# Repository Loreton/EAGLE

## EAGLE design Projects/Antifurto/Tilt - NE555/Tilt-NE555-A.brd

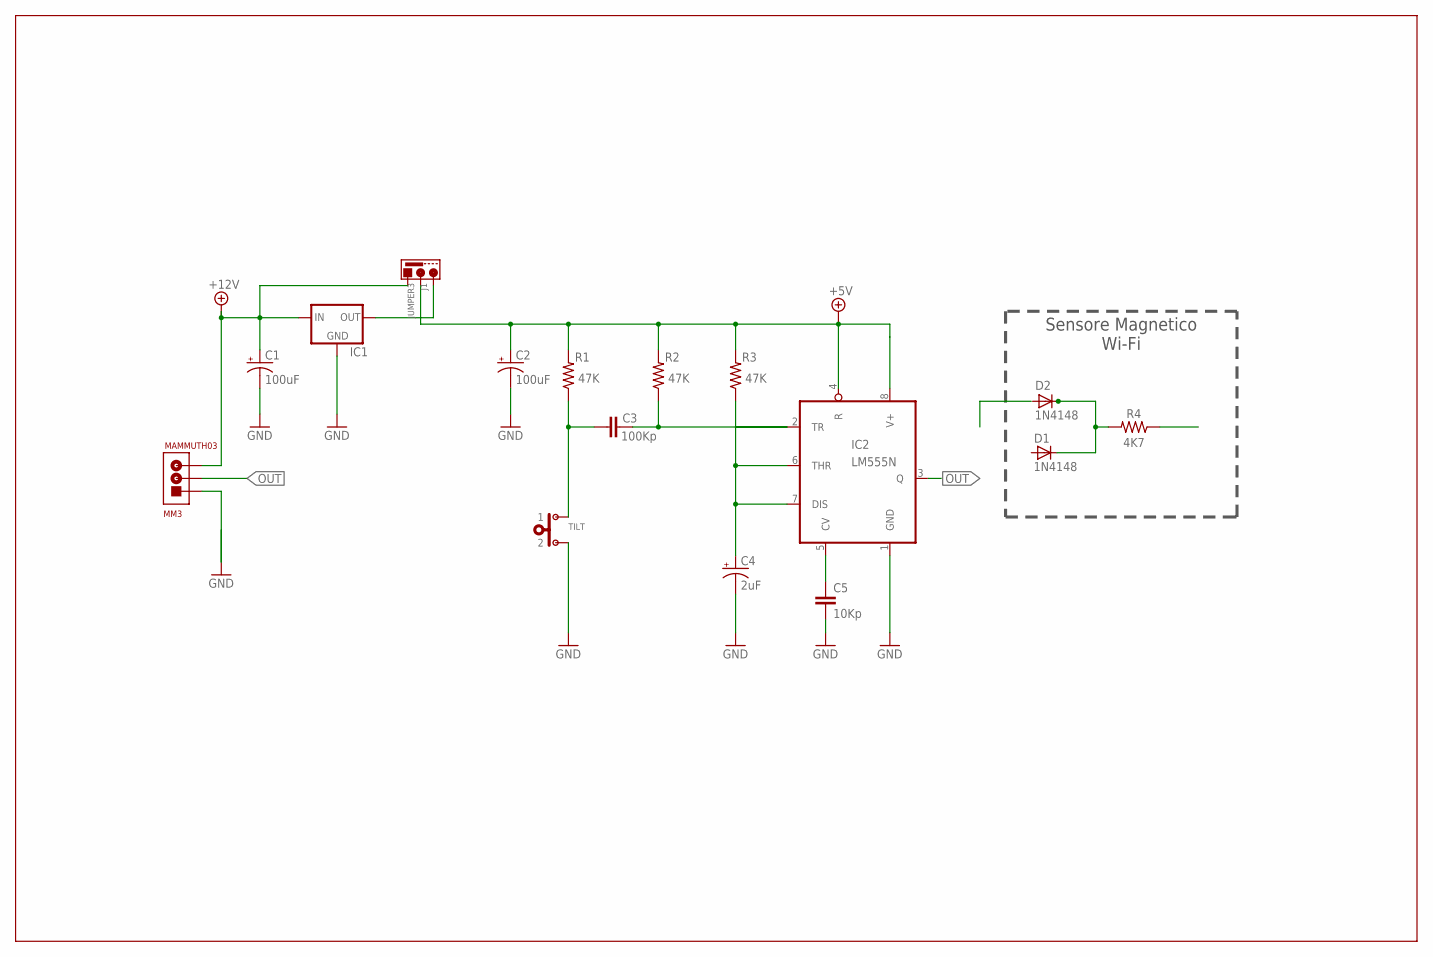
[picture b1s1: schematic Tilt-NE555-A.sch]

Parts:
C1, C2: 100uF; 085CS_1AR
C3: 100Kp; C025-025X050
C4: 2uF; 085CS_1AR
C5: 10Kp; C025-025X050
D1, D2: 1N4148; DO35-10
IC1: 78LXX
IC2: LM555N; DIL08
J1: JUMPER3; SIP03
MM3: MAMMUTH03
R1, R2, R3: 47K; 0207/12
R4: 4K7; 0207/12
TILT: PULSANTENO; SIP02

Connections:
+5V: C2.+, IC2.4 (R), IC2.8 (V+), J1.1, R1.2, R2.2, R3.2
+12V: C1.+, IC1.IN, J1.2, MM3.P$3 (3)
GND: C1.-, C2.-, C4.-, C5.2, IC1.GND, IC2.1 (GND), MM3.P$1 (1), TILT.2
unnamed: C3.2, IC2.2 (TR), R2.1
unnamed: C3.1, R1.1, TILT.1
unnamed: C4.+, IC2.6 (THR), IC2.7 (DIS), R3.1
unnamed: C5.1, IC2.5 (CV)
unnamed: D1.C, D2.C, R4.2
unnamed: IC1.OUT, J1.3
OUT: IC2.3 (Q), MM3.P$2 (2)
SENSORE: R4.1

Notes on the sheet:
Sensore Magnetico Wi-Fi

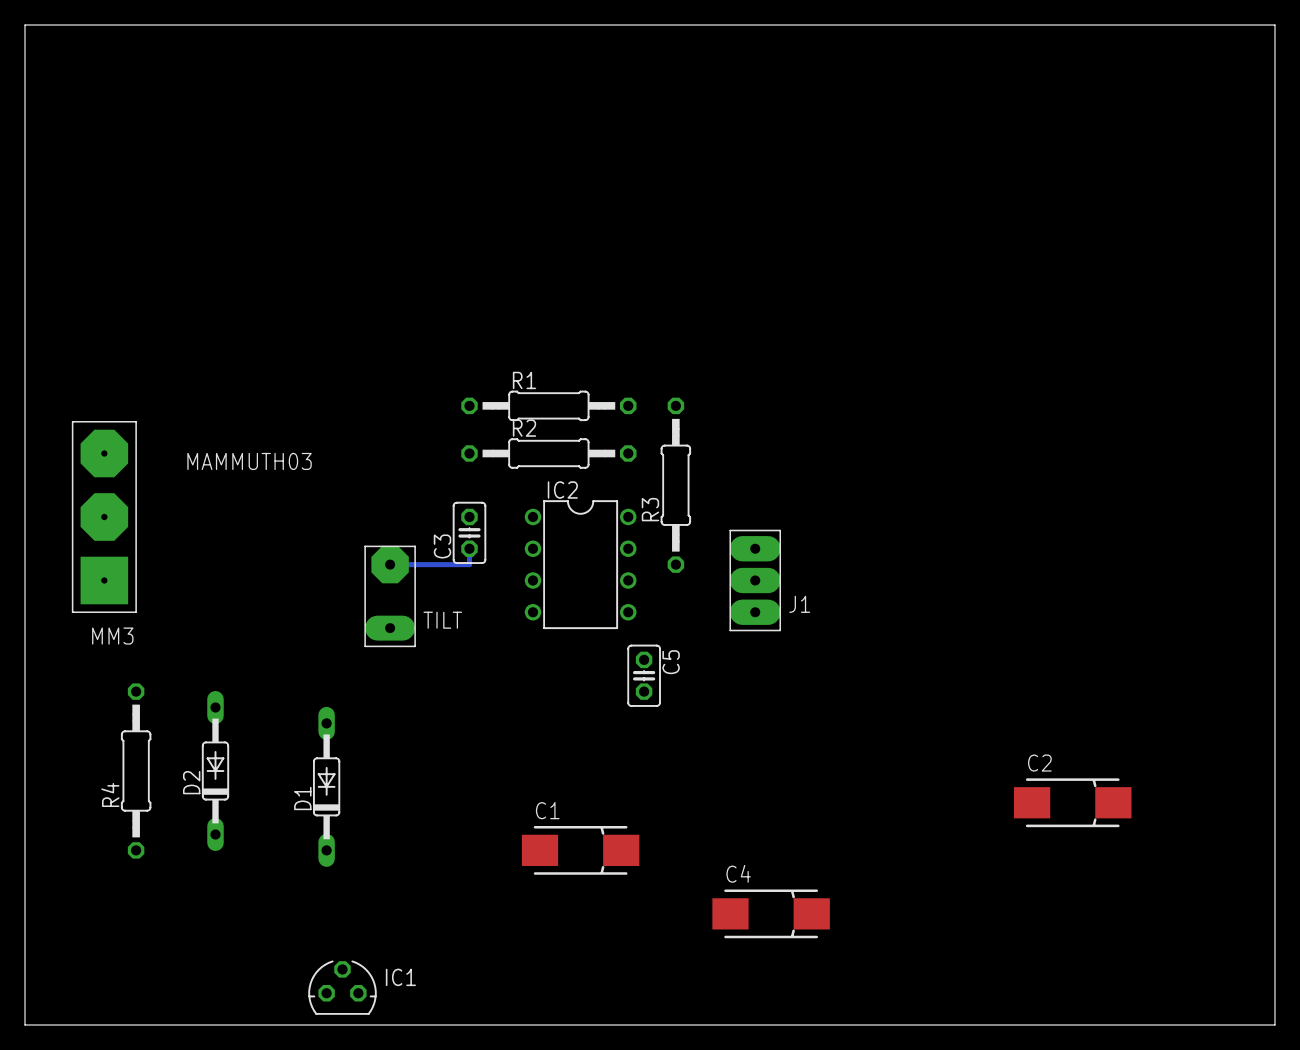
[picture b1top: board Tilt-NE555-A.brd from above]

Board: 2 copper layers, 100.0 x 80.0 mm, 16 parts (0 on the bottom side), 10 nets.

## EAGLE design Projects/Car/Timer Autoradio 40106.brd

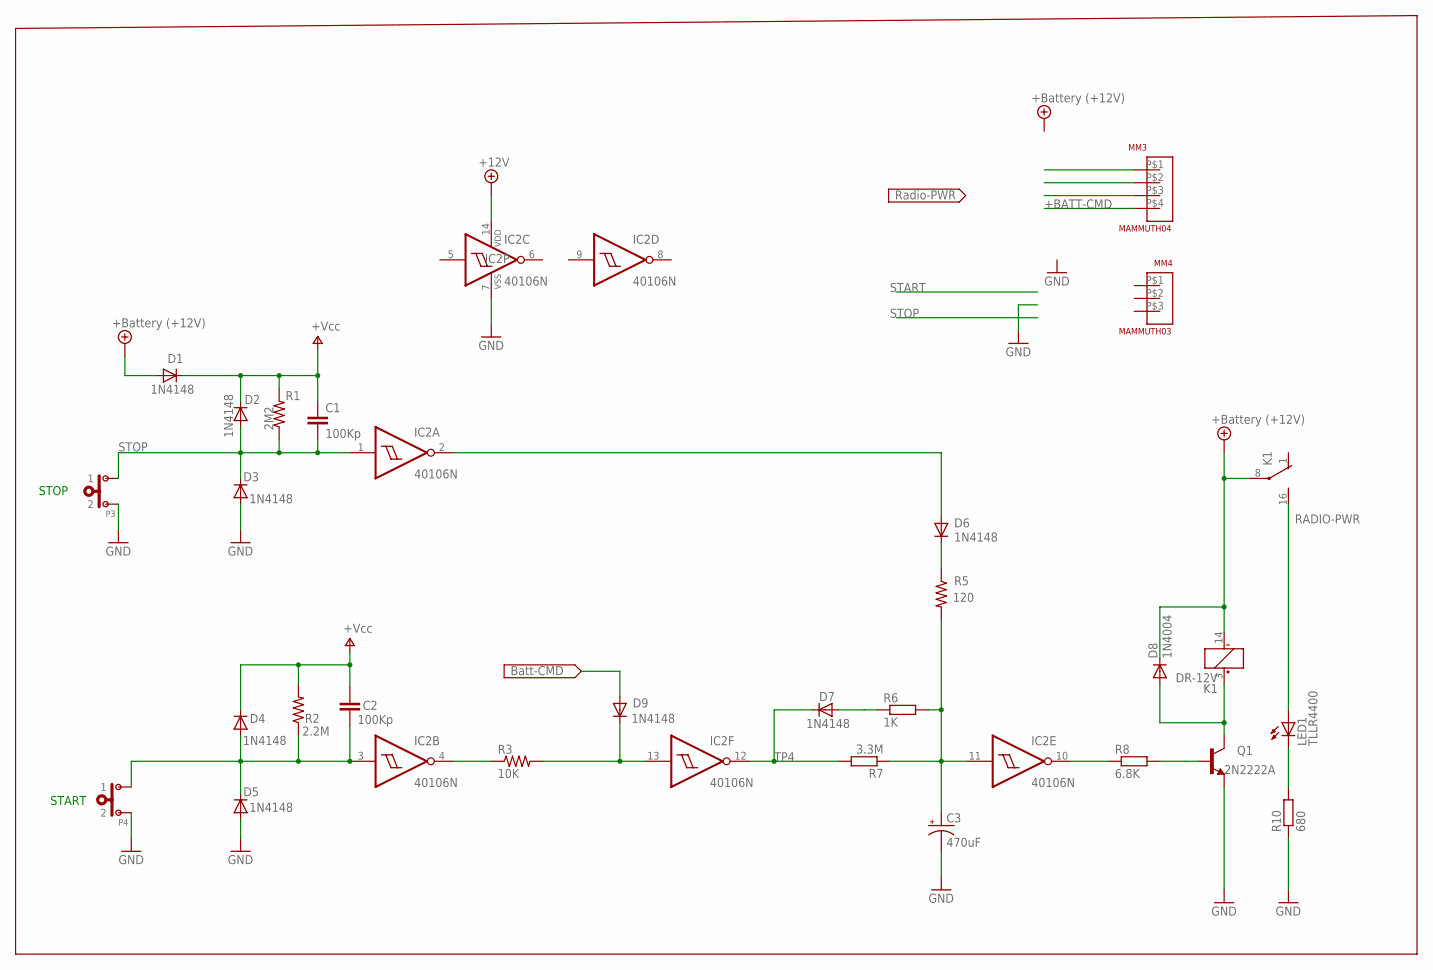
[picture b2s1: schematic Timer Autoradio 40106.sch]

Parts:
C1, C2: 100Kp; C025-025X050
C3: 470uF; E3,5-8
D1, D2, D3, D4, D5, D6, D7, D9: 1N4148; DO35-10
D8: 1N4004; DO41-10
IC2: 40106N; DIL14
K1: DR-12V; DR-1
LED1: TLLR4400; LED3MM
MM3: MAMMUTH04
MM4: MAMMUTH03
P3, P4: PULSANTENO; SIP02
Q1: 2N2222A; TO18
R1: 2M2; 0207/12
R2: 2.2M; 0207/12
R3: 10K; 0207/12
R5: 120; 0207/12
R6: 1K; 0207/10
R7: 3.3M; 0207/10
R8: 6.8K; 0207/10
R10: 680; 0207/10

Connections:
+12V: D1.A, D8.C, IC2.14 (VDD), K1.8, K1.14 (-)
+BATT-CMD: D9.C, R3.2
GND: C3.-, D3.A, D5.A, IC2.7 (VSS), P3.2, P4.2, Q1.1 (E), R10.1
unnamed: C2.2, D4.A, D5.C, IC2.3 (I), P4.1, R2.1
unnamed: Q1.2 (B), R8.2
unnamed: D8.A, K1.3 (+), Q1.3 (C)
unnamed: D6.C, R5.1
unnamed: LED1.K (C), R10.2
RADIO-PWR: K1.16 (S), LED1.A
START: D7.A, R6.1
STOP: C1.2, D2.A, D3.C, IC2.1 (I), P3.1, R1.1
TP4: D7.C, R7.2
TP4A: C3.+, IC2.11 (I), R5.2, R6.2, R7.1
TP5: IC2.10 (O), R8.1
V+: C1.1, C2.1, D1.C, D2.C, D4.C, R1.2, R2.2

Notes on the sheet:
START
STOP

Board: 2 copper layers, 28 parts (0 on the bottom side), 15 nets, no tracks yet.

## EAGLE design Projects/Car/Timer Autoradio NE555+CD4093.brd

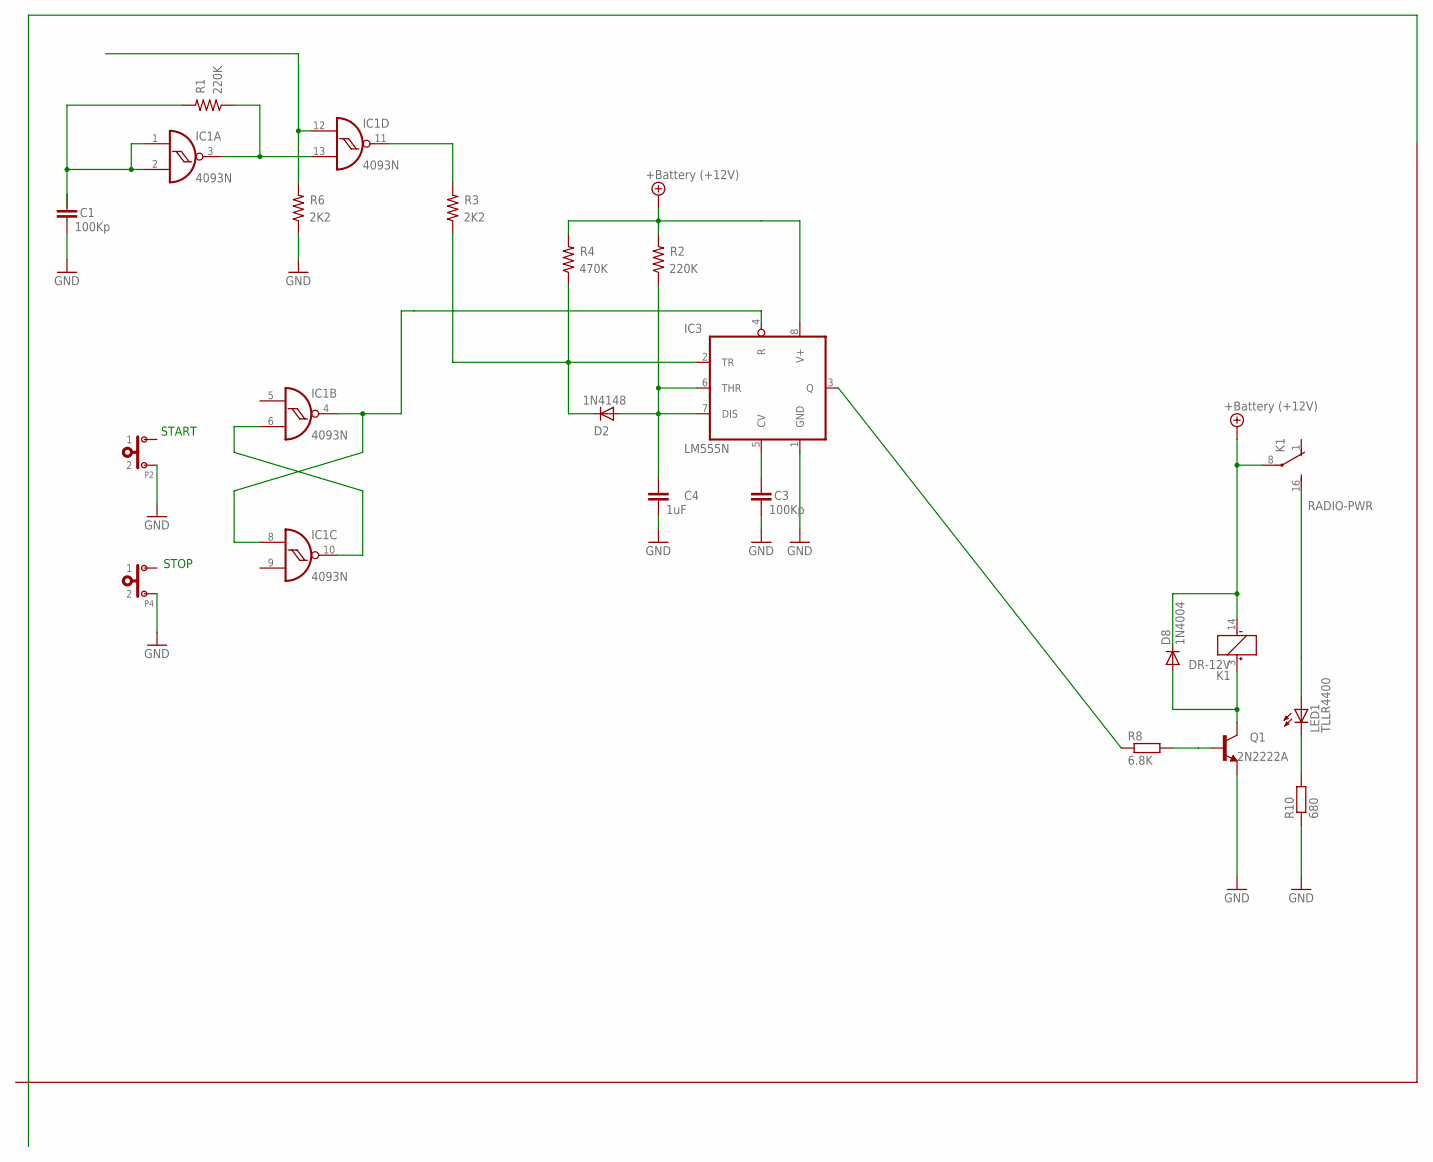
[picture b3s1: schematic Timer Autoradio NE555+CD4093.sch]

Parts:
C1, C3: 100Kp; C025-025X050
C4: 1uF; C025-025X050
D2: 1N4148; DO35-10
D8: 1N4004; DO41-10
IC1: 4093N; DIL14
IC3: LM555N; DIL08
K1: DR-12V; DR-1
LED1: TLLR4400; LED3MM
P2, P4: PULSANTENO; SIP02
Q1: 2N2222A; TO18
R1, R2: 220K; 0207/12
R3, R6: 2K2; 0207/12
R4: 470K; 0207/12
R8: 6.8K; 0207/10
R10: 680; 0207/10

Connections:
+12V: D8.C, IC3.8 (V+), K1.8, K1.14 (-), R2.2, R4.2
GND: IC3.1 (GND), P2.2, P4.2, Q1.1 (E), R6.1, R10.1
unnamed: Q1.2 (B), R8.2
unnamed: D8.A, K1.3 (+), Q1.3 (C)
unnamed: C3.1, IC3.5 (CV)
unnamed: IC1.3 (O), R1.1
unnamed: IC1.12 (I0), R6.2
unnamed: C1.1, IC1.1 (I0), IC1.2 (I1), R1.2
unnamed: LED1.K (C), R10.2
unnamed: IC1.11 (O), R3.2
unnamed: IC3.3 (Q), R8.1
unnamed: IC1.6 (I1), IC1.10 (O)
unnamed: IC1.4 (O), IC1.8 (I0), IC3.4 (R)
unnamed: D2.C, IC3.2 (TR), R3.1, R4.1
unnamed: C4.1, D2.A, IC3.6 (THR), IC3.7 (DIS), R2.1
RADIO-PWR: K1.16 (S), LED1.A
VDD: IC1.14 (VDD)
VSS: IC1.7 (VSS)

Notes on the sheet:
START
STOP

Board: 2 copper layers, 19 parts (0 on the bottom side), 16 nets, no tracks yet.
